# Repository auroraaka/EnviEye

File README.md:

# EnviEye: Air Pollution Monitoring System
A novel, cost-effective, and temperature/humidity drift resilient air pollution monitor for detecting CO2, CO, CH4, NOx, NH3, H2S, and VOCs. Building an open-source database of minute-by-minute air quality in high-risk locations across Massachusetts. In partnership with the MassDEP and sponsored by EPA Enhanced Air Quality Monitoring for Communities Grant.

## Quick Links
- [Sensor Map Database](https://www.environa.org/envieye): location marker database of ThingSpeak channels displaying active data from live EnviEye air pollution monitors
- [Build Guide](https://docs.google.com/presentation/d/e/2PACX-1vTb9qzZoU7ihO3saF2nRVf8Kc_sK2KtpKpaAT560-QxsJg3QxZHz59rv6SrPiSbV5mgcdfRNgG8oTTH/pub?start=false&loop=false&delayms=3000): step-by-step instructional manual slideshow including required components and tools
- [Technical Documentation](https://www.environa.org/_files/ugd/a23aa6_806df408c55a414ab66d8ea2d8b6d26c.pdf): full engineering-based analysis of sensor theory, technology, limitations, and impact
- [IEEE Sensors Paper](https://ieeexplore.ieee.org/document/9812483): discusses how to improve the accuracy of MOS gas sensors in ambient conditions
- [Patent](https://patents.google.com/patent/US20230112016A1/en): establishes intellectual property over sensor innovations

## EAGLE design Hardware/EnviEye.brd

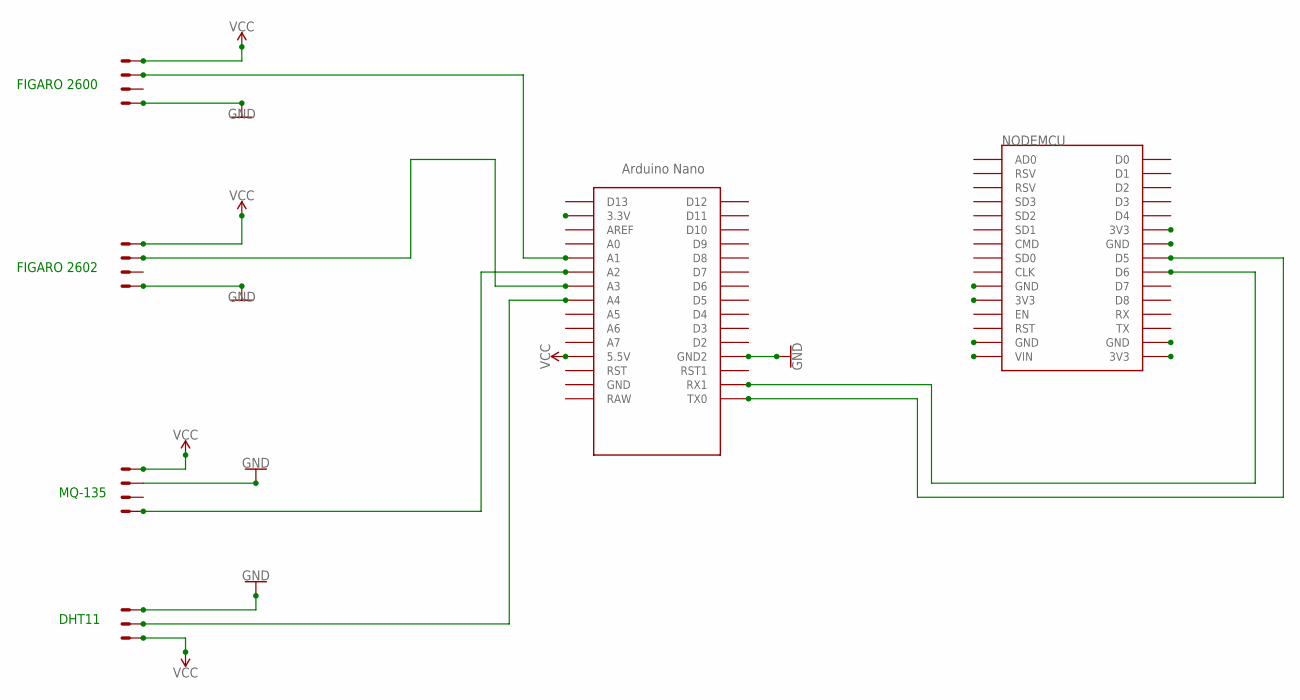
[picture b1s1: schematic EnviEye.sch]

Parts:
DHT11: 22-23-2031
FIGARO2600, FIGARO2602: 22-23-2041
MQ-135: 22-23-2041
NODEMCU: ESP12E_DEVKIT
U$1: NANO

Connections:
GND: DHT11.3, FIGARO2600.4, FIGARO2602.4, MQ-135.2, U$1.GND1 (GND2)
unnamed: FIGARO2600.2, U$1.A3
unnamed: FIGARO2602.2, U$1.A1
unnamed: NODEMCU.D6, U$1.RX1
unnamed: NODEMCU.D5, U$1.TX0
unnamed: DHT11.2, U$1.A4
unnamed: MQ-135.4, U$1.A2
VCC: DHT11.1, FIGARO2600.1, FIGARO2602.1, MQ-135.1, U$1.5V (5.5V)

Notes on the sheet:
MQ-135
DHT11
FIGARO 2602
FIGARO 2600

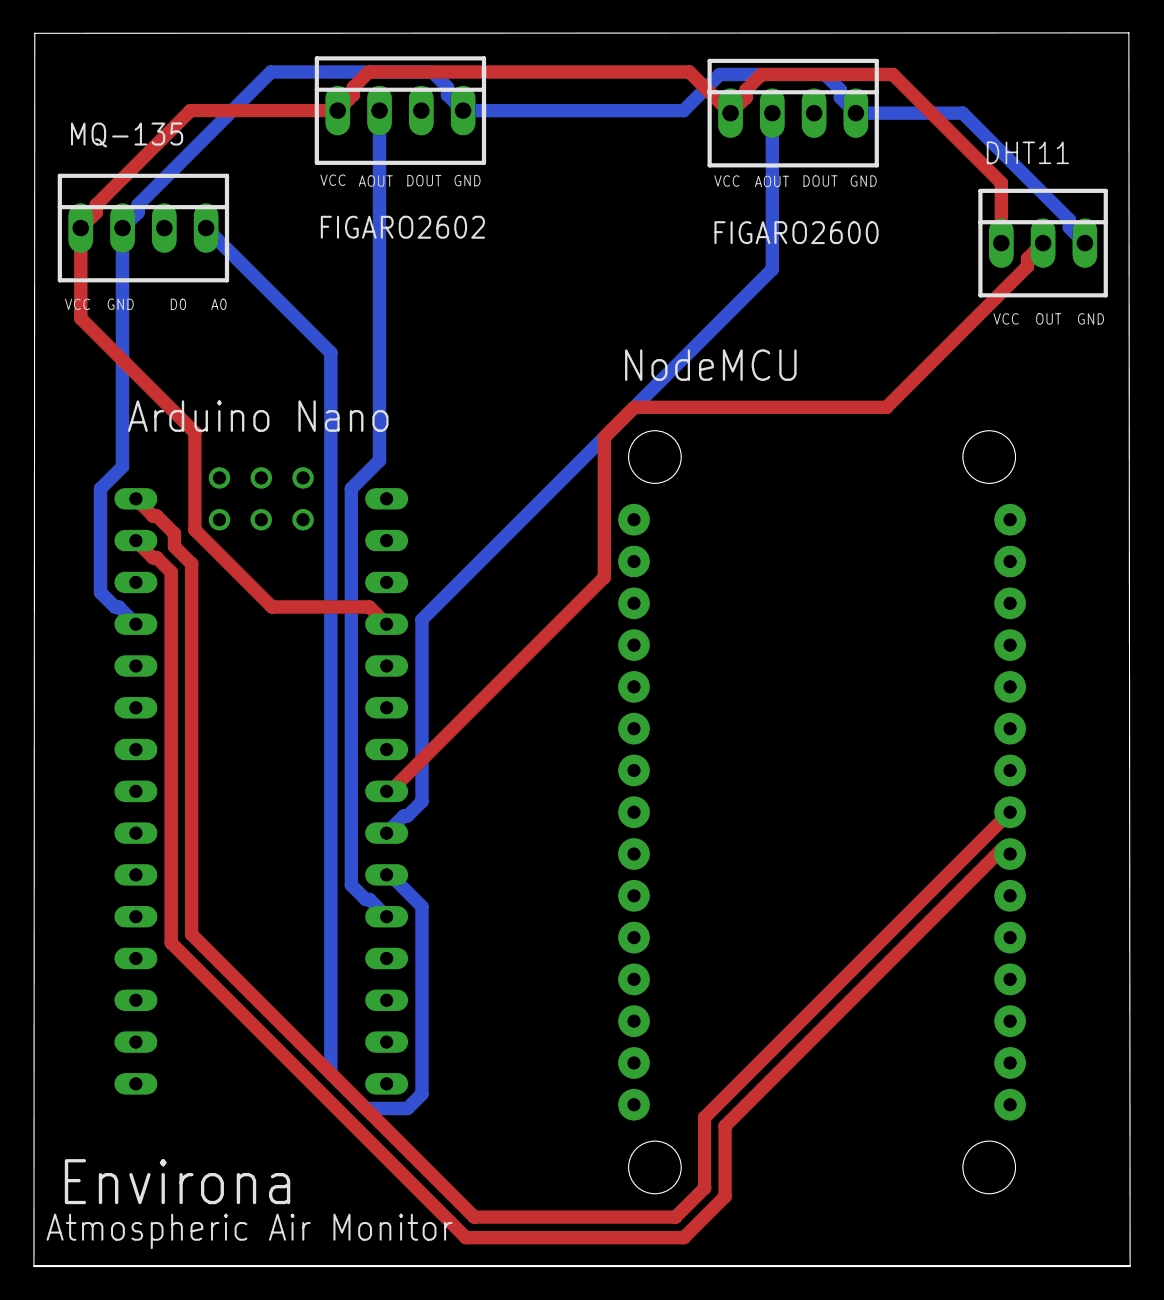
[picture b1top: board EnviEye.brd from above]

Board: 2 copper layers, 66.6 x 74.9 mm, 6 parts (0 on the bottom side), 8 nets.

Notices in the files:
parts and their libraries:
SparkFun-PowerSymbols: Licensing: Creative Commons ShareAlike 4.0 International - https://creativecommons.org/licenses/by-sa/4.0
